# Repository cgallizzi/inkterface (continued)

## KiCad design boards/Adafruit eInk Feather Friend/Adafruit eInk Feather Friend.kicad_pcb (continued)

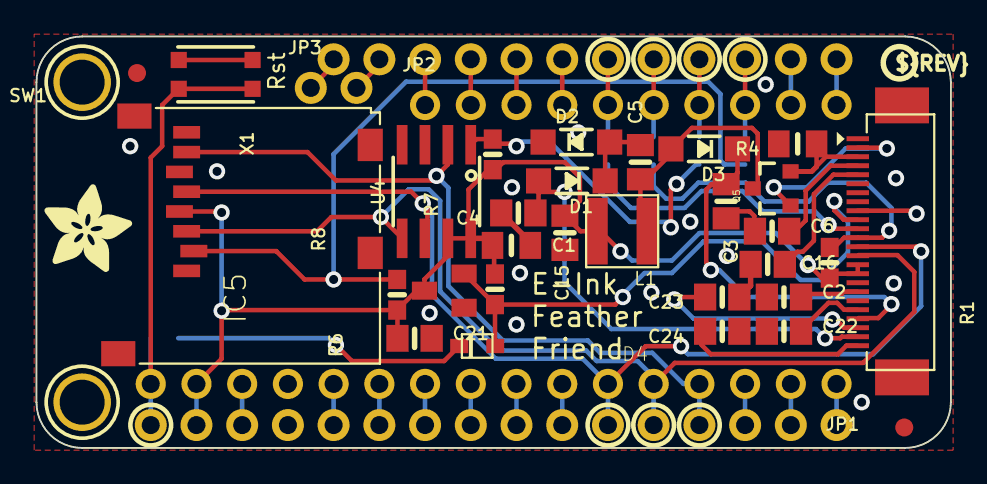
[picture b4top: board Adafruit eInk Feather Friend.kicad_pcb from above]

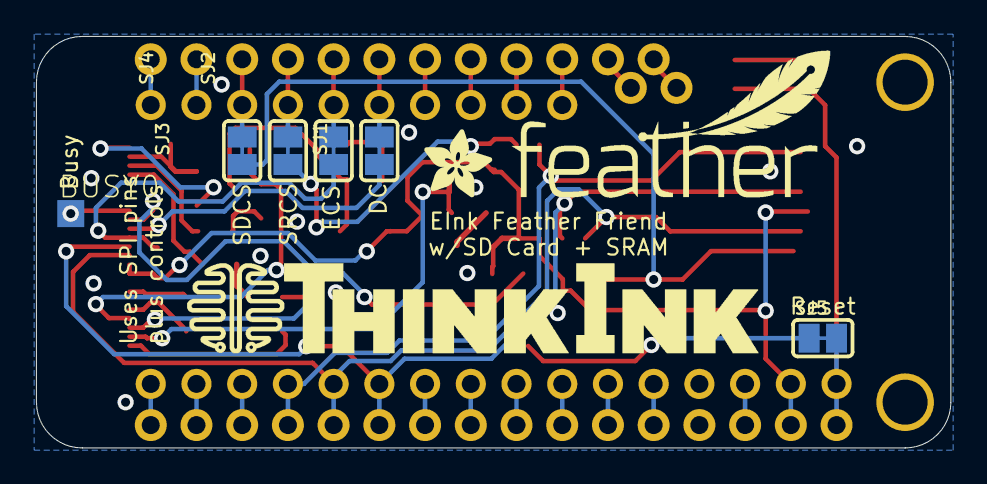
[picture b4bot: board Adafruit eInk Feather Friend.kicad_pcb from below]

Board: 2 copper layers, 50.8 x 22.9 mm, 47 parts (9 on the bottom side), 47 nets.

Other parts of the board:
U$5: THINKINK_1.25IN
U$6: FEATHERLOGO_MED
U$8: ADAFRUIT_5MM
U$9: PCBFEAT-REV-040
U$17: ADAFRUIT_3.5MM

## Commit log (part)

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2025-09-25 Initial commit.
2025-09-25 Begin adding firmware.
2025-09-26 Swap to arduino and adafruit libs for quick first prototype.
2025-09-26 Begin adding some more real drawing operations.
2025-09-30 Start adding BLE handling using NimBLE so we can monitor RSSI.
2025-09-30 Begin adding actual BLE interactions.
2025-09-30 Let macOS builds actually use bluetooth.
2025-09-30 Add some RSSI monitoring.
2025-10-01 Fix characteristic callbacks, use BLE addr for name.
2025-10-01 Add service and characteristic handling.
2025-10-01 Try to gracefully shutdown on a few signals.
2025-10-01 Specify paritions explicitly to disable UF2 usbdrive boot.
2025-10-01 Use gitrev instead of datetime.
2025-10-01 Embed git rev into fw.
2025-10-01 Begin actually structuring status inputs.
2025-10-01 Allow actually setting the labels and discrete values.
2025-10-01 Restrict connections to really nearby units.
2025-10-01 Begin adding actual state collection.
2025-10-01 Fix issues loading steam and bios versions.
2025-10-02 Add actual transport of points.
2025-10-02 Be a little easier on connection restrictions.
2025-10-02 Enhance some graphics, thicker lines, better corners, etc.
2025-10-02 Actually read back some data and pipe it through.
2025-10-02 Load current steam user.
2025-10-02 Fix missing double quote.
2025-10-02 Handle flat lines better, remove some debug logging.
2025-10-02 Adjust rssi sensitivity and discovery time.
2025-10-02 Ignore cached results.
2025-10-02 Tweak again.
2025-10-03 Begin adding steam stubs.
2025-10-07 Begin adding some experimental partial screen refresh handling.
2025-10-07 Fix current user on other plats, capture app start/stop.
2025-10-07 Begin adding some experiments with slurping data from mangohud.
2025-10-07 Fix msg queue interactions.
2025-10-07 Add some functions to send mangohud control messages.
2025-10-07 Include tls plugin for QNetwork connections.
2025-10-07 Allow using account names rather than persona names in some cases.
2025-10-07 Adjust mangohud logging control, fall back to mangohudctl.
2025-10-07 Add injestion and management of mangohud logs to provide some statistics.
2025-10-07 Remove non-ascii characters from name, reset points for new apps and logs.
2025-10-07 No need to check underflow, type is unsigned.
2025-10-07 Include more points when parsing mangohud logs.
2025-10-09 Mangohud locks up and after some time, maybe cycling it's UI helps?
2025-10-10 Add option to install self as service on linux.
2025-10-10 Handle case where app is bundled into appimage.
2025-10-13 Add some logging, fix bug where we stop updating stats.
2025-10-13 Shrink sparkboxes a little.
2025-10-13 Collect mangohud and system stats on different intervals.
2025-10-13 Allow for up to 32 points in sparklines.
2025-10-13 Double point size we keep and transmit.
2025-10-17 Add readme.
2025-11-13 Add gabe image, will process into splash screen for display.
2025-11-13 Add gabe image boot splash.
2025-11-21 Fix bug where we show "Playing" when not playing anything.
2025-12-11 Make logo match actual design.
2026-02-24 Specify --pull to avoid initial package install issues.
    Only affects users who have been using distrobox images but may not have
    pulled a new achrlinux:base-devel image in a long time.
2026-03-22 Add container def for better builds, use git revision as version when possible.
2026-03-22 Explicitly ignore unused return values here.
2026-03-23 Begin adding some ui components.
2026-03-23 Actually use name filtering.
2026-03-27 Bring in some updates and new shared QML elements.
2026-03-27 Service should always run in --headless mode.
2026-03-27 Don't create tarball package for dirty workspace.
2026-03-29 Run qmlformat with config on all QML files.
2026-03-31 Add more details to mockup.
2026-04-16 Begin refactoring for UI.
2026-04-17 Start setting up frunk listing.
2026-04-23 Add some more UI components, remove MANGO from name.
2026-04-28 Try out using an SVG frunk.
2026-05-01 Show interface version on display.
2026-05-01 Sort frunks by supported -> rssi -> name.
2026-05-01 Adjust frunk icon and panel, begin making better list page.
2026-05-01 Rework pages to use settings, swap between list and config.
2026-05-01 Show frunk name in larger text when waiting on connection.
2026-05-03 Adjust color of unsupported indicator.
2026-05-03 Add more styles and colors to VBevelRect.
2026-05-03 Allow for easier pure mouse nav, handle focus return to list.
2026-05-04 Handle resizing better, setup for managing service.
2026-05-04 Adjust to use name from settings, don't grab mango stats.
2026-05-04 Begin adding class to manage systemd service.
2026-05-04 Begin stubbing in service manager.
2026-05-04 Make sure we can actually create and chown QT_ROOT.
2026-05-04 Add first pass at service management.
2026-05-04 Make a copy without the version flag in filename.
2026-05-05 Log exit code when checking service.
2026-05-05 Add a custom log handler that rotates file logs.
2026-05-05 Handle cases where exit code is in the high byte.
2026-05-05 Handle cases where screen size is oddly small.
    This is mostly for my tiny display front panels.
2026-05-05 Thinking about how to handle configurable panels.
2026-05-05 Begin documenting new stats we can collect.
2026-05-06 Add a bunch of documentation.
2026-05-06 Add some notes for different things to display.
2026-05-07 Begin migrating system stat colleciton away from Frunk.
2026-05-07 Flesh out system stats.
2026-05-07 Refactor Frunk to use SysStats instead of manually loading.
2026-05-08 Swap to use local VDF parsing rather than always relying on Steam API.
2026-05-08 Add a gaben svg.
2026-05-08 Cleanup stats notes, adjust point window and send interval.
2026-05-08 Include min/max y values for each sparkline.
2026-05-08 Need to ensure single precision floats.
2026-05-08 Show ymin and ymax in sparklines.
2026-05-08 Test out reducing sparkline range from 0xFFFF to 0xFF.
2026-05-08 Smooth out annoying fluctuations for graph.
2026-05-08 Update to reflect new size with smaller points.
2026-05-08 Don't need so many points in cycle.
    Too many points causes sparklines to overlap and become unclear.
2026-05-08 Don't round points.
    Doesn't really help, no sense in loosing precision for nothing.
2026-05-10 Add installed app count.
2026-05-11 Add ability to invert colors.
    Looks kinda awful in some states, but we can tweak it.
2026-05-11 Add getting average CPU clock.
2026-05-11 Add ability to restart service, run QML formatter.
2026-05-11 Use app count and fix it up slightly.
    Still not quite right. The library folders VDF file may not get flushed
    frequently enough so we may want to just scan for app manifest files in
    the libraries it does list.
2026-05-11 Begin migrating frunk state management to it's own class.
    This also adds a first pass at configurable and registerable data
    collectors.
2026-05-11 Steam instance should track running app details.
2026-05-11 Log settings path to help with debugging.
2026-05-11 Fix bevel rect lines outside of container.
2026-05-11 Make frunk a little easier to select.
2026-05-11 Refactor frunk state so we can view and configure the fields.
    And now external other additions can register custom collectors for
    other types of data and automatically have them populate through the UI
    for users to select.
2026-05-11 Remove coming soon label, configuration exists now.
2026-05-11 Allow manually setting VSparkline value.
2026-05-11 When collecting points, any new point is a change.
2026-05-12 Begin cleaning up to make frunk use FrunkFinder and FrunkState.
2026-05-12 Continue refactoring Frunk.
2026-05-12 Ignore .user files generated by Qt Creator.
2026-05-12 Fix some clazy analysis warnings.
2026-05-12 Finish reworking Frunk to use FrunkFinder for discovery.
2026-05-12 Don't bother showing RSSI and interface version, just clutter.
2026-05-12 Let bounds be zero until we have points, set length to actual point length.
2026-05-13 If we lose our connection we should restart discovery.
2026-05-14 Copy unbranded version of appimage into dist folder at end.
2026-05-14 For floating point types min is smallest non-zero, we want lowest.
2026-05-14 Don't collect CPU usage from /proc/stat more than once per second.
    Fixes a bug where we were getting a good value for the string labels but
    then immediately reading again for our sparklines and getting a very
    small and useless value.
2026-05-14 Fully clear connection when disconnected, only discover services when connected.
2026-05-21 Add store asset images.
2026-05-21 Try making error and disconnect states more robust.
2026-05-21 Add some logging around service install and setup for steamworks deploy.
2026-05-21 Make service state detection more robust.
2026-05-21 Swap std::system usage for QProcess::execute
2026-05-21 Swap to interact with systemd via dbus, much better.
2026-05-29 Disconnect from frunk if it fails comms for too long.
2026-05-29 Gate some actions based on service state.
2026-05-29 Bring in board files eink breakout and feather friend.
2026-05-30 Map the rest of the component models to the breakout board.
2026-05-30 Use TE 2-2492111-4 model for FPC connector, is actually JUSHUO AFC07-S24ECA-00.
    JUSHUO part doesn't have an easily available model, but it does appear
    to be a nearly identical clone of the TE part, available on LCSC. This
    model matches all critical dimensions.
2026-05-30 Bring in feather board and begin placing component CAD.
2026-06-05 Just search for app manifests instead of trusting the library vdf.
    The library metadata vdf files are not necessarily flushed to disk after
    all operations, so when installing/uninstalling games we can get out of
    sync. But the appmanifests should be generated and flushed so we can
    just scan for those.
2026-06-05 Remove unecessary includes, run clang-format on svcmgr.
2026-06-05 Fix bug where we wouldn't pick up games running at startup.
    Also fixes issue where we over or under emit changes to running apps.
2026-06-09 Add support for breakout epd board.
2026-06-11 Disable service management except on Linux.
2026-06-11 Try putting esp32 into light sleep.
    Need to enable some more system configuration that I'm not entirely sure
    works with the Arduino framework. I'd rather switch to ESP-IDF but I
    also don't want to alienate folks who aren't familiar with it since so
    many people are familiar with Arduino.
2026-06-11 Add some images of the boards from kicad.
2026-06-12 Update design/store assets to rename Frunk Manager to Inkterface.
2026-06-12 Remove old configuration.
2026-06-12 Remove RSSI limiting, we explicitly configure connections.
2026-06-12 Rename panel from FRUNK to INKTF.
2026-06-12 Rename project from mango-frunk to inkterface. Thx JohnnyD!
2026-06-12 Fix deploy with new project name.
2026-06-12 Add 256px icon.
2026-06-12 Inkterface has capital I.
2026-06-12 Add CAD for 3D printed enclosure.
2026-06-12 Add some links and an assembly guide.
2026-06-12 Note in the firmware build setup that you can use the container.
2026-06-12 Add an assembly tutorial video.
2026-06-13 Include pin names in wiring diagram.
2026-06-15 Add some manual folding and run through clang-format.
2026-06-15 Add documentation for fuel gauge on feather, and begin testing it.
2026-06-16 Display battery state, only update when it actually changes.
2026-06-18 Show charge reminder when battery is low. Print debug to RX/TX pins.
2026-06-24 Don't show percentage, maybe re-enable if we train/config the fuel gauge.
2026-06-24 Add license file and note to readme.
2026-06-24 Make startup delay and startup splash optional.
2026-06-24 Add assembly guide pages to design mockup.
2026-06-24 Add STL's for folks that can't easily use STEP files.
2026-06-25 Add assembly pdf.
2026-06-25 Adjust assembly guide.
2026-06-25 Add software setup guide.
2026-06-25 Update readme to point to new docs and have better usage instructions.
2026-06-25 Fix bug where we sometimes get stuck advertising/not advertising.
    Not sure why these callbacks seem to fail, and this actually might not
    handle the loss of connection still, but we can also track last comms
    for this too.
